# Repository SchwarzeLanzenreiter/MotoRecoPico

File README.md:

# MotoRecoPico

A CAN + GPS data logger for motorcycles. A home-made board carrying a **Raspberry Pi Pico 2
(RP2350)** records the vehicle's CAN bus and GPS to a microSD card. The resulting files open
directly in [MotoRecoViewer](https://github.com/SchwarzeLanzenreiter/MotoRecoViewer).

This is [MotoRecoLogger](https://github.com/SchwarzeLanzenreiter/MotoRecoLogger) — which ran on a
Raspberry Pi plus a HAT — collapsed onto a single board. The recording format is compatible, so old
and new logs read with the same tools.

## Repository layout

| Directory | Contents |
|---|---|
| [`firmware/`](firmware/) | Firmware for the Pico 2 (C / pico-sdk). See [firmware/README.md](firmware/README.md) |
| `cad/kicad/` | KiCad 10 project, fabrication data, generation and inspection scripts |
| `cad/electronics/` | The old EAGLE version (reference only; KiCad is current) |
| [`docs/`](docs/) | Design documents. **[netlist.md](docs/netlist.md) is the canonical description of the circuit** |

## Hardware

| Item | Details |
|---|---|
| Board | 4 layers, 21 × 61 mm, 41 components. The only leaded parts are J1, Y1 and the Pico header |
| MCU | Raspberry Pi Pico 2 (RP2350). Replaceable, in a 2×20 socket. Moved to the back side in v4.2 |
| CAN | Microchip MCP25625 (controller and transceiver in one), driven over SPI1 |
| GPS | YIC GT-502MGG-N. NMEA over UART0 at 9600 bps |
| Storage | microSD (Hirose DM3AT-SF-PEJM5) over SPI0 |
| Vehicle I/F | TE MQS .63, 8 way. Only 5 of them are used: permanent 12V, IG, CAN High, CAN Low, GND |
| Power | 12V → AP63205 buck converter → 5V. The 3.3V rail comes from the Pico's 3V3(OUT) |

**Power is held up for about 0.55 s (measured) after the key goes off.** C13 holds the gate charge
of the high-side switch, and the firmware uses that grace period to close the log. The contract is
in [netlist.md](docs/netlist.md) §4.7.

How the design got here — why four layers, why this placement, what each revision fixed — is
recorded in [netlist.md](docs/netlist.md) and [hardware-design.md](docs/hardware-design.md).
Where to buy the parts is in [parts-sourcing.md](docs/parts-sourcing.md).

## Firmware

- Runs as a **single loop**. There are only two interrupts: CAN reception and the GPS UART
- CAN reception is moved into a ring buffer by the interrupt, so the controller's two-stage FIFO
  does not overflow even when an SD write blocks for hundreds of milliseconds
- NMEA is parsed in-house (replacing gpsd on the Pi version). There is no RTC, so GPS time is
  pinned to the monotonic clock
- FatFs R0.16 is bundled. The SPI block driver for the SD card is our own
- A log is finalized **only on IG OFF detection**. CAN engine speed is not used, to keep
  vehicle-specific knowledge out of the firmware
- The time zone is configured through a hidden file `MOTORECO.CFG` on the microSD card (no rebuild)
- The hardware-independent parts (NMEA, encoding, settings, IG decision, clock) **have tests that
  run on a bare Pico 2 or on a PC**

Build instructions, how to read the logs, and troubleshooting are in
[firmware/README.md](firmware/README.md).

## Recording format (`.dat`)

A sequence of fixed-length 16-byte records. No header, no delimiters, everything little-endian.

| Offset | Type | Contents |
|---|---|---|
| 0 | `uint32` | Seconds since the log started |
| 4 | `uint16` | Milliseconds within that second |
| 6 | `uint16` | CAN ID (standard 11-bit) |
| 8 | `uint8[8]` | Payload (zero-padded when DLC is less than 8) |

GPS rides on CAN IDs that cannot exist, as fixed-point values. **`0x7FF`** carries longitude and
latitude, **`0x7FE`** carries altitude and speed. That way CAN and GPS land in one single time
series.

**`0x7FD`** (added for MotoNavi, not written by the Pi version) carries the absolute time of each
fix, since the record time above only counts from the start of the log. One per fix, written when
the fix's GGA sentence arrives and after any `0x7FF` that sentence produced, so it pairs with the
`0x7FF` at or just before it. It is written while standing still too, when `0x7FF` is skipped
because the position has not changed:

| Bytes | Contents |
|---|---|
| 0–5 | UTC of the fix, Unix milliseconds, 48-bit little-endian |
| 6 | Fix kind in the high nibble (0 none, 1 2D, 2 3D, 3 DGPS/SBAS/RTK), satellites used in the low nibble (15 = 15 or more) |
| 7 | HDOP × 10, rounded (255 = 25.5 or more, 0 = not reported) |

The time of day, satellites and HDOP all come from that GGA. GGA has no date, so the date is
taken from the last RMC with a fix, and nothing is written before the first one. GGA rather than
RMC because the receiver sends GSA and GSV between the two on every fifth fix, which made an
RMC-timed frame arrive about 45 ms late on those fixes only.
Readers that do not know `0x7FD` skip it like any other ID.

> This format is a **contract shared with MotoRecoLogger (the Pi version) and MotoRecoViewer**;
> changing it affects all three repositories. `0x7FF`, `0x7FE` and `0x7FD` are reserved in every
> MotoReco repository.

File names are `YYYYMMDD_HHMMSS.dat` (key-off time, local time). The date is unknown until GPS gets
a fix, so recording starts into `TMPnnnnn.DAT` and the file is renamed to the start time once a fix
arrives.

## Status

- **Verified on the bike with both CAN and GPS recording** (2026-09)
- The board is v4.2. Real operation was confirmed on a physical v4.1 board (v4.2 is identical in
  parts, nets and GPIO assignment)
- Not yet confirmed: an end-to-end check of opening a recorded `.dat` in MotoRecoViewer

## Related repositories

- [MotoRecoLogger](https://github.com/SchwarzeLanzenreiter/MotoRecoLogger) — the logger daemon for
  the Raspberry Pi; this firmware was ported from it
- [MotoRecoViewer](https://github.com/SchwarzeLanzenreiter/MotoRecoViewer) — the Windows
  application that views the recorded `.dat` files

## License

MIT License ([LICENSE](LICENSE)).

The bundled ChaN FatFs is covered by its own license
([firmware/third_party/fatfs/LICENSE.txt](firmware/third_party/fatfs/LICENSE.txt)).

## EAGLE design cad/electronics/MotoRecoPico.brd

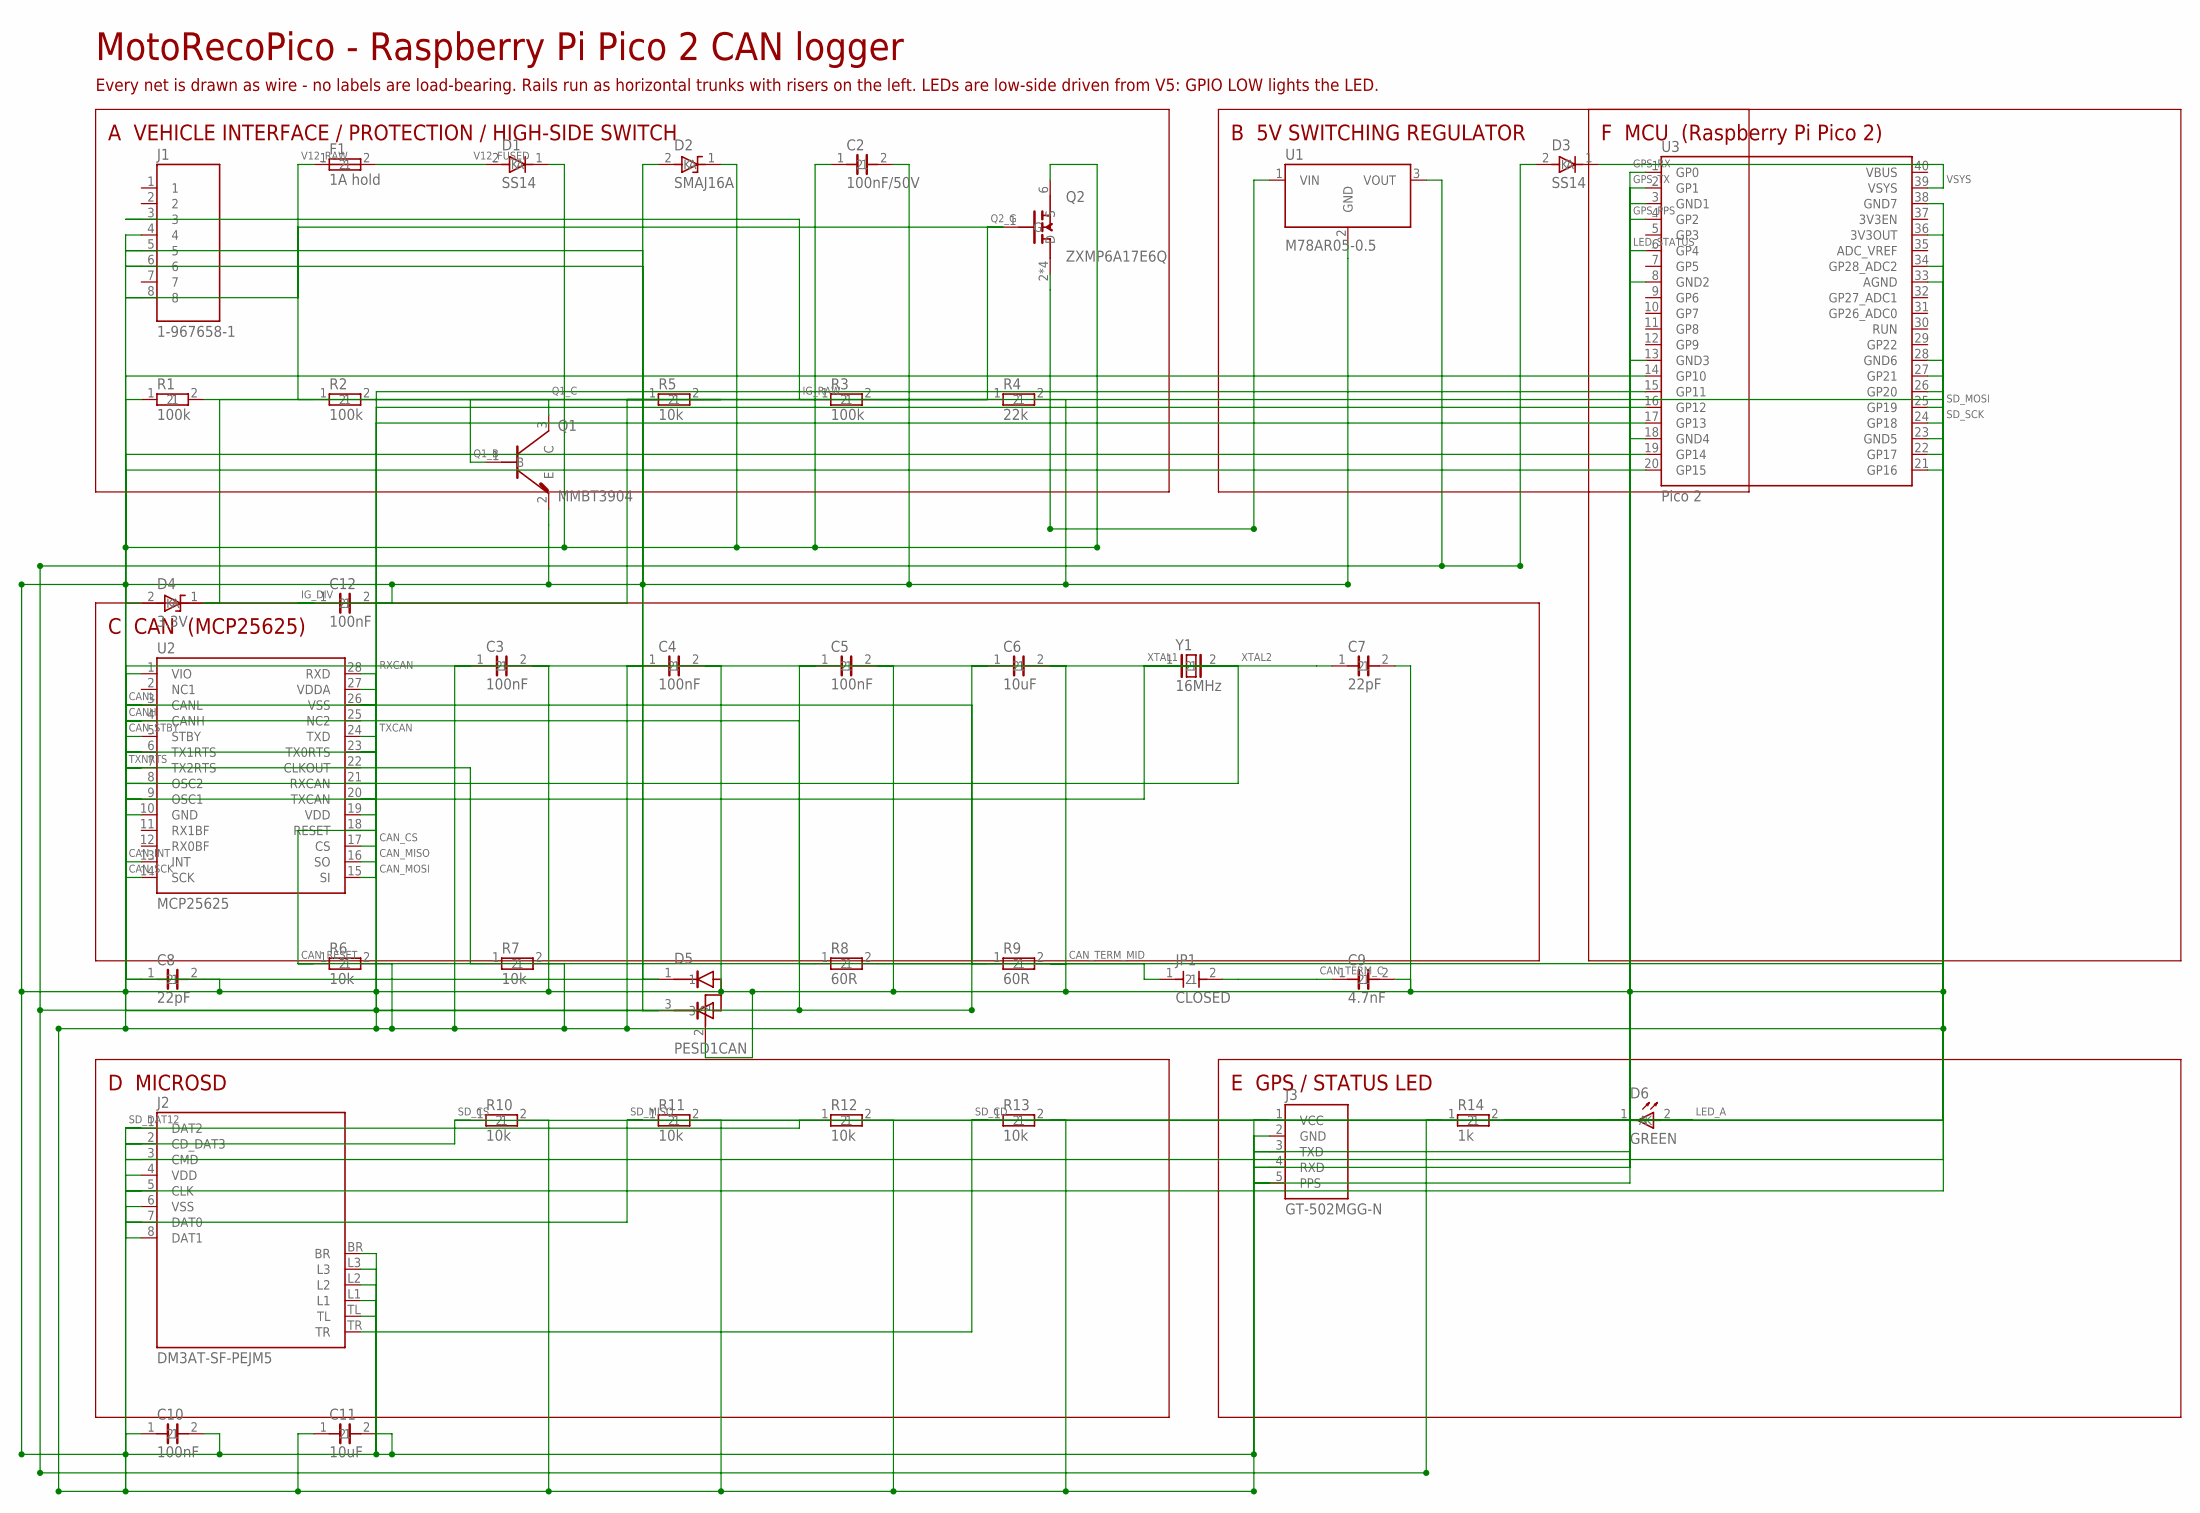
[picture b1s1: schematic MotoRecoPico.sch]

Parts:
C2: 100nF/50V; C1005
C3, C4, C5, C10, C12: 100nF; C1005
C6, C11: 10uF; C1608
C7, C8: 22pF; C1005
C9: 4.7nF; C1005
D1, D3: SS14; SOD123
D2: SMAJ16A; SMA
D4: 3.3V; SOD123
D5: PESD1CAN; SOT23
D6: GREEN; LED-SIDE-2812
F1: 1A hold; C1206
J1: 1-967658-1; MQS-8-RA-967658
J2: DM3AT-SF-PEJM5; MICROSD-DM3AT
J3: GT-502MGG-N; GPS-5P-SMD
JP1: CLOSED; SJ2
Q1: MMBT3904; SOT23
Q2: ZXMP6A17E6Q; SOT26
R1, R2, R3: 100k; C1005
R4: 22k; C1005
R5, R6, R7, R10, R11, R12, R13: 10k; C1005
R8, R9: 60R; C1005
R14: 1k; C1005
U1: M78AR05-0.5; SIP3-M78AR05
U2: MCP25625; SSOP28
U3: Pico 2; RPI-PICO2-THT
Y1: 16MHz; HC49S

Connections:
CANH: D5.1, J1.6, R8.1, U2.4 (CANH)
CANL: D5.3, J1.5, R9.1, U2.3 (CANL)
CAN_CS: U2.17 (CS), U3.17 (GP13)
CAN_INT: U2.13 (INT), U3.19 (GP14)
CAN_MISO: U2.16 (SO), U3.16 (GP12)
CAN_MOSI: U2.15 (SI), U3.15 (GP11)
CAN_RESET: R6.1, U2.18 (RESET), U3.26 (GP20)
CAN_SCK: U2.14 (SCK), U3.14 (GP10)
CAN_STBY: U2.5 (STBY), U3.20 (GP15)
CAN_TERM_C: C9.1, JP1.2
CAN_TERM_MID: JP1.1, R8.2, R9.2
GND: C2.2, C3.2, C4.2, C5.2, C6.2, C7.2, C8.2, C9.2, C10.2, C11.2, C12.2, D2.2 (A), D4.2 (A), D5.2, J1.4, J2.6 (VSS), J2.BR, J2.L1, J2.L2, J2.L3, J2.TL, J3.2 (GND), Q1.2 (E), R4.2, U1.2 (GND), U2.10 (GND), U2.26 (VSS), U3.3 (GND1), U3.8 (GND2), U3.13 (GND3), U3.18 (GND4), U3.23 (GND5), U3.28 (GND6), U3.33 (AGND), U3.38 (GND7)
GPS_PPS: J3.5 (PPS), U3.4 (GP2)
GPS_RX: J3.4 (RXD), U3.1 (GP0)
GPS_TX: J3.3 (TXD), U3.2 (GP1)
IG_DIV: C12.1, D4.1 (K), R3.2, R4.1, R5.1, U3.34 (GP28_ADC2)
IG_RAW: J1.3, R3.1
LED_A: D6.2 (A), R14.2
LED_STATUS: D6.1 (K), U3.6 (GP4)
Q1_B: Q1.1 (B), R5.2
Q1_C: Q1.3 (C), R2.2
Q2_G: Q2.1 (G), R1.2, R2.1
RXCAN: U2.21 (RXCAN), U2.28 (RXD)
SD_CD: J2.TR, R13.1, U3.27 (GP21)
SD_CS: J2.2 (CD_DAT3), R10.1, U3.22 (GP17)
SD_DAT12: J2.1 (DAT2), J2.8 (DAT1), R12.1
SD_MISO: J2.7 (DAT0), R11.1, U3.21 (GP16)
SD_MOSI: J2.3 (CMD), U3.25 (GP19)
SD_SCK: J2.5 (CLK), U3.24 (GP18)
TXCAN: U2.20 (TXCAN), U2.24 (TXD)
TXNRTS: R7.1, U2.6 (TX1RTS), U2.7 (TX2RTS), U2.23 (TX0RTS)
V3V3: C3.1, C4.1, C10.1, C11.1, J2.4 (VDD), J3.1 (VCC), R6.2, R7.2, R10.2, R11.2, R12.2, R13.2, U2.1 (VIO), U2.19 (VDD), U3.36 (3V3OUT)
V5: C5.1, C6.1, D3.2 (A), R14.1, U1.3 (VOUT), U2.27 (VDDA)
V12P: C2.1, D1.1 (K), D2.1 (K), Q2.6 (S), R1.1
V12_FUSED: D1.2 (A), F1.2
V12_RAW: F1.1, J1.8
V12_SW: Q2.2 (D), Q2.3 (D), Q2.4 (D), Q2.5 (D), U1.1 (VIN)
VSYS: D3.1 (K), U3.39 (VSYS)
XTAL1: C7.1, U2.9 (OSC1), Y1.1
XTAL2: C8.1, U2.8 (OSC2), Y1.2

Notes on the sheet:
A VEHICLE INTERFACE / PROTECTION / HIGH-SIDE SWITCH
B 5V SWITCHING REGULATOR
C CAN (MCP25625)
F MCU (Raspberry Pi Pico 2)
D MICROSD
E GPS / STATUS LED
MotoRecoPico - Raspberry Pi Pico 2 CAN logger
Every net is drawn as wire - no labels are load-bearing. Rails run as horizontal trunks with risers on the left. LEDs are low-side driven from V5: GPIO LOW lights the LED.

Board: 1 copper layer, 42 parts (15 on the bottom side), 40 nets, no tracks yet.

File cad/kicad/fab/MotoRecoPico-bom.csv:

"Designator","Comment","Footprint","Qty"
"C2","100nF/50V","Capacitor_SMD:C_0603_1608Metric","1"
"C3","100nF","Capacitor_SMD:C_0603_1608Metric","1"
"C4","100nF","Capacitor_SMD:C_0603_1608Metric","1"
"C5","100nF","Capacitor_SMD:C_0603_1608Metric","1"
"C6","10uF","Capacitor_SMD:C_0603_1608Metric","1"
"C7","22pF","Capacitor_SMD:C_0603_1608Metric","1"
"C8","22pF","Capacitor_SMD:C_0603_1608Metric","1"
"C10","100nF","Capacitor_SMD:C_0603_1608Metric","1"
"C11","10uF","Capacitor_SMD:C_0603_1608Metric","1"
"C13","10uF/25V","Capacitor_SMD:C_0603_1608Metric","1"
"C14","10uF/50V","Capacitor_SMD:C_1206_3216Metric","1"
"C15","22uF/16V","Capacitor_SMD:C_0805_2012Metric","1"
"C16","100nF/50V","Capacitor_SMD:C_0805_2012Metric","1"
"D1","B5819W","Diode_SMD:D_SOD-123","1"
"D2","SMAJ16A","Diode_SMD:D_SMA","1"
"D3","B5819W","Diode_SMD:D_SOD-123","1"
"D6","GREEN","MotoRecoPico:LED-SideView-2.8x1.2","1"
"F1","1A hold","Fuse:Fuse_1206_3216Metric","1"
"J2","DM3AT-SF-PEJM5","Connector_Card:microSD_HC_Hirose_DM3AT-SF-PEJM5","1"
"J3","GT-502MGG-N","MotoRecoPico:GPS-5P-SMD-2.54","1"
"L1","6.8uH","MotoRecoPico:L_4030_HandSolder","1"
"Q1","MMBT3904","Package_TO_SOT_SMD:SOT-23","1"
"Q2","ZXMP6A17E6Q","Package_TO_SOT_SMD:TSOT-23-6_HandSoldering","1"
"R1","100k","Resistor_SMD:R_0603_1608Metric","1"
"R2","100k","Resistor_SMD:R_0603_1608Metric","1"
"R3","100k","Resistor_SMD:R_0603_1608Metric","1"
"R4","22k","Resistor_SMD:R_0603_1608Metric","1"
"R6","10k","Resistor_SMD:R_0603_1608Metric","1"
"R7","10k","Resistor_SMD:R_0603_1608Metric","1"
"R8","120","Resistor_SMD:R_0603_1608Metric","1"
"R10","10k","Resistor_SMD:R_0603_1608Metric","1"
"R11","10k","Resistor_SMD:R_0603_1608Metric","1"
"R12","10k","Resistor_SMD:R_0603_1608Metric","1"
"R13","10k","Resistor_SMD:R_0603_1608Metric","1"
"R14","1k","Resistor_SMD:R_0603_1608Metric","1"
"R15","10k","Resistor_SMD:R_0603_1608Metric","1"
"U2","MCP25625","Package_SO:SSOP-28_5.3x10.2mm_P0.65mm","1"
"U4","AP63205WU-7","Package_TO_SOT_SMD:TSOT-23-6_HandSoldering","1"

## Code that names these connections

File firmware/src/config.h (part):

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// ---------------------------------------------------------------------------

// microSD on SPI0
#define PIN_SD_SCK		2
#define PIN_SD_MOSI		3
#define PIN_SD_MISO		4
#define PIN_SD_CS		5	// driven as plain GPIO, not the SPI hardware CSn
#define PIN_SD_CD		7	// card detect switch, external 10k pull up (R13)

// GPS GT-502MGG-N on UART0
#define PIN_GPS_TX		0	// pico -> module RXD (green wire)
#define PIN_GPS_RX		1	// module TXD (orange wire) -> pico
#define PIN_GPS_PPS		6	// not used yet. kept so the pin is not repurposed by accident

// green LED. the only indicator on the board. driven low side from 5V, so LOW lights it
#define PIN_LED			8

// CAN controller MCP25625 on SPI1
#define PIN_CAN_INT		9	// active low, open drain on the MCP25625 side
#define PIN_CAN_SCK		10
#define PIN_CAN_MOSI	11
#define PIN_CAN_MISO	12
#define PIN_CAN_CS		13	// driven as plain GPIO, not the SPI hardware CSn
#define PIN_CAN_STBY	20	// high puts the transceiver in standby
#define PIN_CAN_RESET	21	// active low, has a 10k pull up (R6)

// ignition sense. unchanged by the v4.1 rotation
#define PIN_IG_SENSE	28
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
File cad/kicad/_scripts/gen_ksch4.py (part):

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    ('U2', '9'), ('Y1', '1'), ('C7', '1'), ('U2', '8'), ('Y1', '2'), ('C8', '1'),
    ('R14', '2'), ('D6', '2'),
}
# labels dropped onto hand wires (net, x, y, angle) - CANH/CANL reach J1 by
# name, VSYS reaches the Pico
HAND_LABELS = [
    ('CANH', 74, 99, 0, 'left'), ('CANL', 74, 101, 0, 'left'),
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    HANDLED.update({('Y1', '3'), ('Y1', '2'), ('Y1', '4')})
    HAND_LABELS.append(('GND', 70, 120, 0, 'right'))
    # J4 connects purely by name: its stubs are auto-labelled, so the J1-F1
    # wire needs the matching label to merge into one V12_RAW net
    HAND_LABELS.append(('V12_RAW', 30, 33, 0, 'left'))
    NOTES.append(("J4: direct-wire pads on the Pico face (V=12V I=IGN G=GND H=CANH L=CANL)", 18, 66))
    HAND_POWER[:] = [hp for hp in HAND_POWER
                     if (hp[1], hp[2]) not in ((281, 166), (290, 151))]
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

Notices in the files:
firmware/src/config.h:
Copyright (c) 2026 Schwarze Lanzenreiter
